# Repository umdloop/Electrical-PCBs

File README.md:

# ELECTRICAL PCBs

This repository contains all PCBs for UMD Loop's 2025-26 rover, Palamedes.

-----

## Guidelines
* Fork this repository for development, you can open a pull request to this repo to add your changes for everyone.
* Do NOT force push.
* Follow best practices (descriptive commit messages, well documented code, etc.)
* Add a new subdirectory for each PCB that is made

## Including Libraries
* The following libraries tab will include the Digikey, or product vendor component, CAD, Schematic, and/or Drawing for the components that are not found on KiCAD

## Including Datasheets
* The following datasheets tab includes useful information when referencing the components you need to include on the board

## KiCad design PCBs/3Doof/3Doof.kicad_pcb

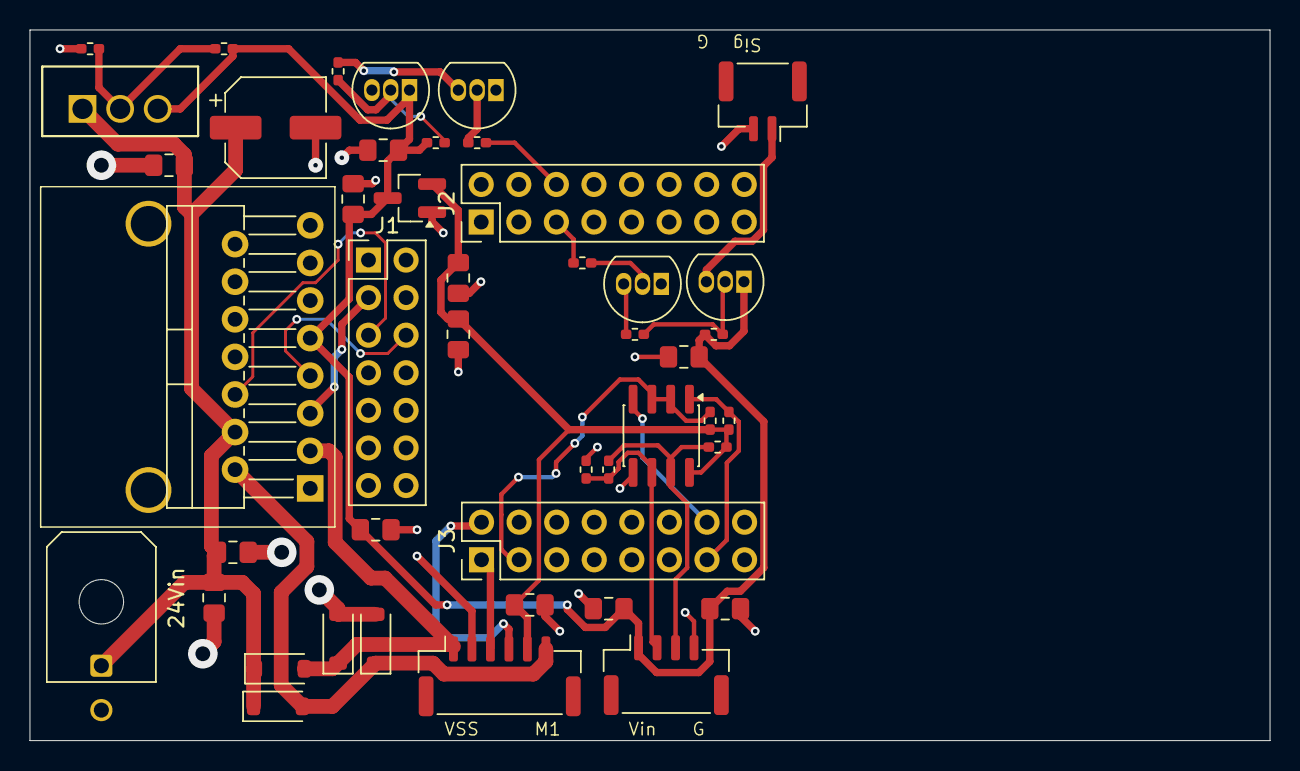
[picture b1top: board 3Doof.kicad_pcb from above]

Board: 2 copper layers, 83.8 x 48.0 mm, 47 parts (0 on the bottom side), 26 nets.

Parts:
24Vin: 24Vin; Molex_Micro-Fit_3.0_43045-0200_2x01_P3.00mm_Horizontal
CHBA1: 10uf; C_0805_2012Metric_Pad1.18x1.45mm_HandSolder
CHBA2: 100nf; C_0805_2012Metric_Pad1.18x1.45mm_HandSolder
CHBA3: 470uf; CP_Elec_6.3x7.7
CHBA4: 10u; C_0805_2012Metric_Pad1.18x1.45mm_HandSolder
CLD1: 10u; C_0805_2012Metric_Pad1.18x1.45mm_HandSolder
CRS1: 100n; C_0805_2012Metric_Pad1.18x1.45mm_HandSolder
CRS2, CRS3: 10u; C_0805_2012Metric_Pad1.18x1.45mm_HandSolder
CServoA1: 10u; C_0805_2012Metric_Pad1.18x1.45mm_HandSolder
CVin: 10u; C_0805_2012Metric_Pad1.18x1.45mm_HandSolder
CVregA1, CVregA3, CVregA4: 100n; C_0805_2012Metric_Pad1.18x1.45mm_HandSolder
DHBA1, DHBA2, DHBA3, DHBA4: 1N4148WT; D_SOD-123
H1, H2: MountingHole; MountingHole_3.2mm_M3
J1: Conn_02x07_Odd_Even; PinHeader_2x07_P2.54mm_Vertical
J2, J3: Conn_02x08_Odd_Even; PinHeader_2x08_P2.54mm_Vertical
J9: Laser Diode; JST_GH_SM02B-GHS-TB_1x02-1MP_P1.25mm_Horizontal
J12: RS485; JST_GH_SM04B-GHS-TB_1x04-1MP_P1.25mm_Horizontal
J14: HBA; JST_GH_SM06B-GHS-TB_1x06-1MP_P1.25mm_Horizontal
LaserDiodeT1: S8550; TO-92_Inline
Q1: QServoA; TO-92_Inline
Q6: LaserDiodeT; TO-92_Inline
QServoA1: S8550; TO-92_Inline
RLD1, RLD5: 220; R_0402_1005Metric_Pad0.72x0.64mm_HandSolder
RLD2: 330; R_0402_1005Metric_Pad0.72x0.64mm_HandSolder
RLD3: 680; R_0402_1005Metric_Pad0.72x0.64mm_HandSolder
RRS2, RRS3: 10K; R_0402_1005Metric_Pad0.72x0.64mm_HandSolder
RRS4, RRS5: 20K; R_0402_1005Metric_Pad0.72x0.64mm_HandSolder
RRS6: 120; R_0402_1005Metric_Pad0.72x0.64mm_HandSolder
RServoA1: 220; R_0402_1005Metric_Pad0.72x0.64mm_HandSolder
RServoA2: 330; R_0402_1005Metric_Pad0.72x0.64mm_HandSolder
RServoA3, RServoA6: 680; R_0402_1005Metric_Pad0.72x0.64mm_HandSolder
U1: MAX485E; SOIC-8_3.9x4.9mm_P1.27mm
U2: LM7805_TO220; T03B
U3: LM7805_TO220; SOT-23_Handsoldering
UHBA1: L298N; l298n_with_heatsink

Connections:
+3.3V: CHBA4.1, CRS2.2, CVregA3.1, J2.16, J14.5, RRS2.1, RRS3.1, RRS5.1, U1.8 (VCC), U3.2 (Vout)
+5V: CHBA1.1, CLD1.2, CRS1.2, CRS3.1, CServoA1.2, CVregA4.1, J12.1, LaserDiodeT1.1 (E), QServoA1.1 (E), RLD2.2, RLD5.1, RServoA2.2, U2.3 (VO), U3.3 (Vin), UHBA1.9 (Vss)
+24V: 24Vin.1, CHBA2.1, CHBA3.1, CVin.1, CVregA1.2, DHBA1.1 (K), DHBA3.1 (K), U2.1 (VI), UHBA1.4 (Vs)
/9: J1.3, UHBA1.5 (IN1)
/10: J1.6, UHBA1.7 (IN2)
/11: J1.5, UHBA1.6 (EnA)
/33: J3.13, RRS3.2, U1.1 (RO)
/35: J3.14, U1.4 (DI)
/41: J3.3, RRS2.2, U1.2 (~RE), U1.3 (DE)
/42: J3.2, J14.4
/43: J3.1, J14.3
/58: J2.5, RLD1.1
/59: J2.6, RServoA1.1
GND: 24Vin.2, CHBA1.2, CHBA2.2, CHBA3.2, CHBA4.2, CLD1.1, CRS1.1, CRS2.1, CRS3.2, CServoA1.1, CVin.2, CVregA1.1, CVregA3.2, CVregA4.2, DHBA2.2 (A), DHBA4.2 (A), J2.15, J9.2, J12.4, J14.2, Q1.1 (E), Q6.1 (E), RRS4.2, RServoA6.1, U1.5 (GND), U3.1 (GND), UHBA1.1 (SENSE_A), UHBA1.8 (GND), UHBA1.15 (SENSE_B)
unnamed: DHBA1.2 (A), DHBA2.1 (K), J14.6, UHBA1.2 (OUT1)
unnamed: DHBA3.2 (A), DHBA4.1 (K), J14.1, UHBA1.3 (OUT2)
unnamed: J9.1, LaserDiodeT1.3 (C)
unnamed: J12.2, RRS4.1, RRS6.1, U1.6 (A)
unnamed: J12.3, RRS5.2, RRS6.2, U1.7 (B)
unnamed: LaserDiodeT1.2 (B), RLD2.1, RLD3.2
unnamed: Q1.2 (B), RServoA1.2
unnamed: Q1.3 (C), RServoA3.1
unnamed: Q6.2 (B), RLD1.2
unnamed: Q6.3 (C), RLD3.1
unnamed: QServoA1.2 (B), RServoA2.1, RServoA3.2
unnamed: RLD5.2, RServoA6.2, U2.2 (GND)

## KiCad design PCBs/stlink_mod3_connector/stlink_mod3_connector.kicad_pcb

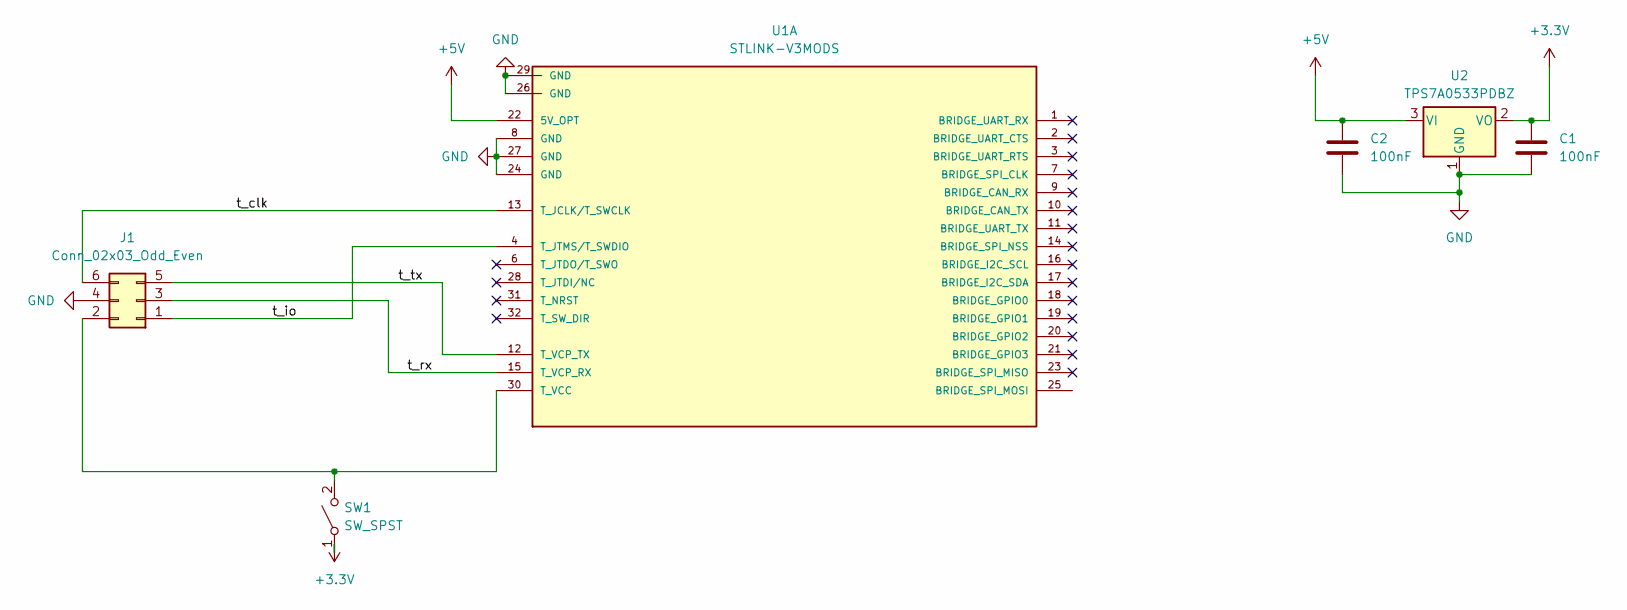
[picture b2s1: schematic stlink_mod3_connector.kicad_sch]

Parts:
C1, C2: 100nF; C_0805_2012Metric_Pad1.18x1.45mm_HandSolder
J1: Conn_02x03_Odd_Even; PinHeader_2x03_P2.54mm_Horizontal
SW1: SW_SPST; slide_switch_2_pin
U1: STLINK-V3MODS; MODULE_STLINK-V3MODS; PARTREV 1; DigiKey_Part_Number 497-STLINK-V3MODS-ND
U2: TPS7A0533PDBZ; SOT-23

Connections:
+3.3V: C1.1, SW1.1 (A), U2.2 (VO)
+5V: C2.1, U1.22 (5V_OPT), U2.3 (VI)
/t_clk: J1.6, U1.13 (T_JCLK/T_SWCLK)
/t_io: J1.1, U1.4 (T_JTMS/T_SWDIO)
/t_rx: J1.3, U1.15 (T_VCP_RX)
/t_tx: J1.5, U1.12 (T_VCP_TX)
GND: C1.2, C2.2, J1.4, U1.8 (GND), U1.24 (GND), U1.26 (GND), U1.27 (GND), U1.29 (GND), U2.1 (GND)
unnamed: J1.2, SW1.2 (B), U1.30 (T_VCC)

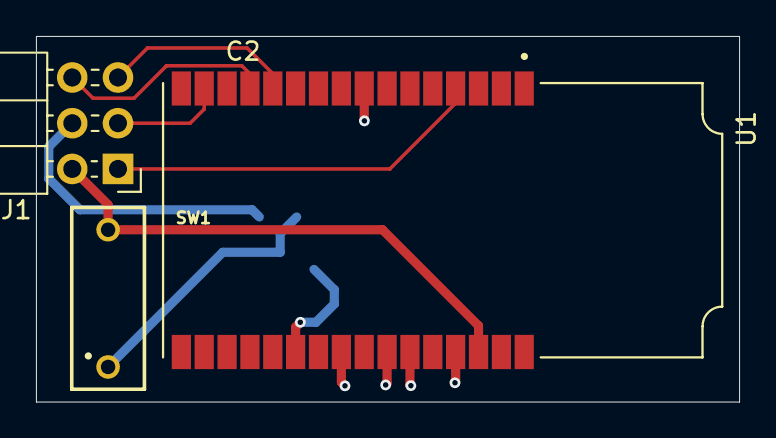
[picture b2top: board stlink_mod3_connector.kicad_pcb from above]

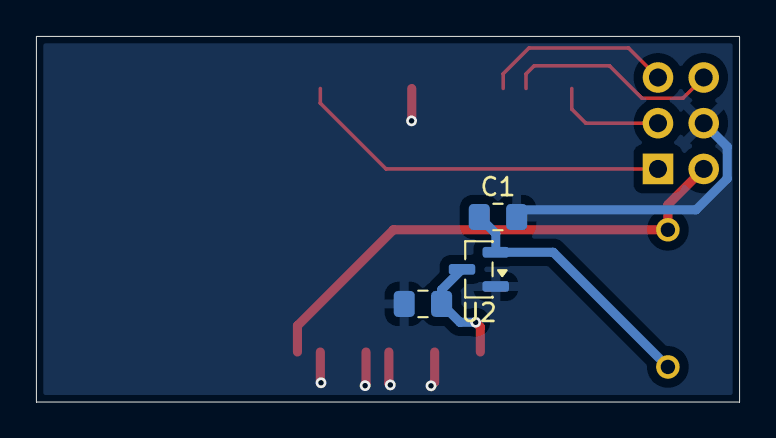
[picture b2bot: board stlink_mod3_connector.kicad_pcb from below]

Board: 2 copper layers, 39.1 x 20.3 mm, 6 parts (3 on the bottom side), 8 nets.

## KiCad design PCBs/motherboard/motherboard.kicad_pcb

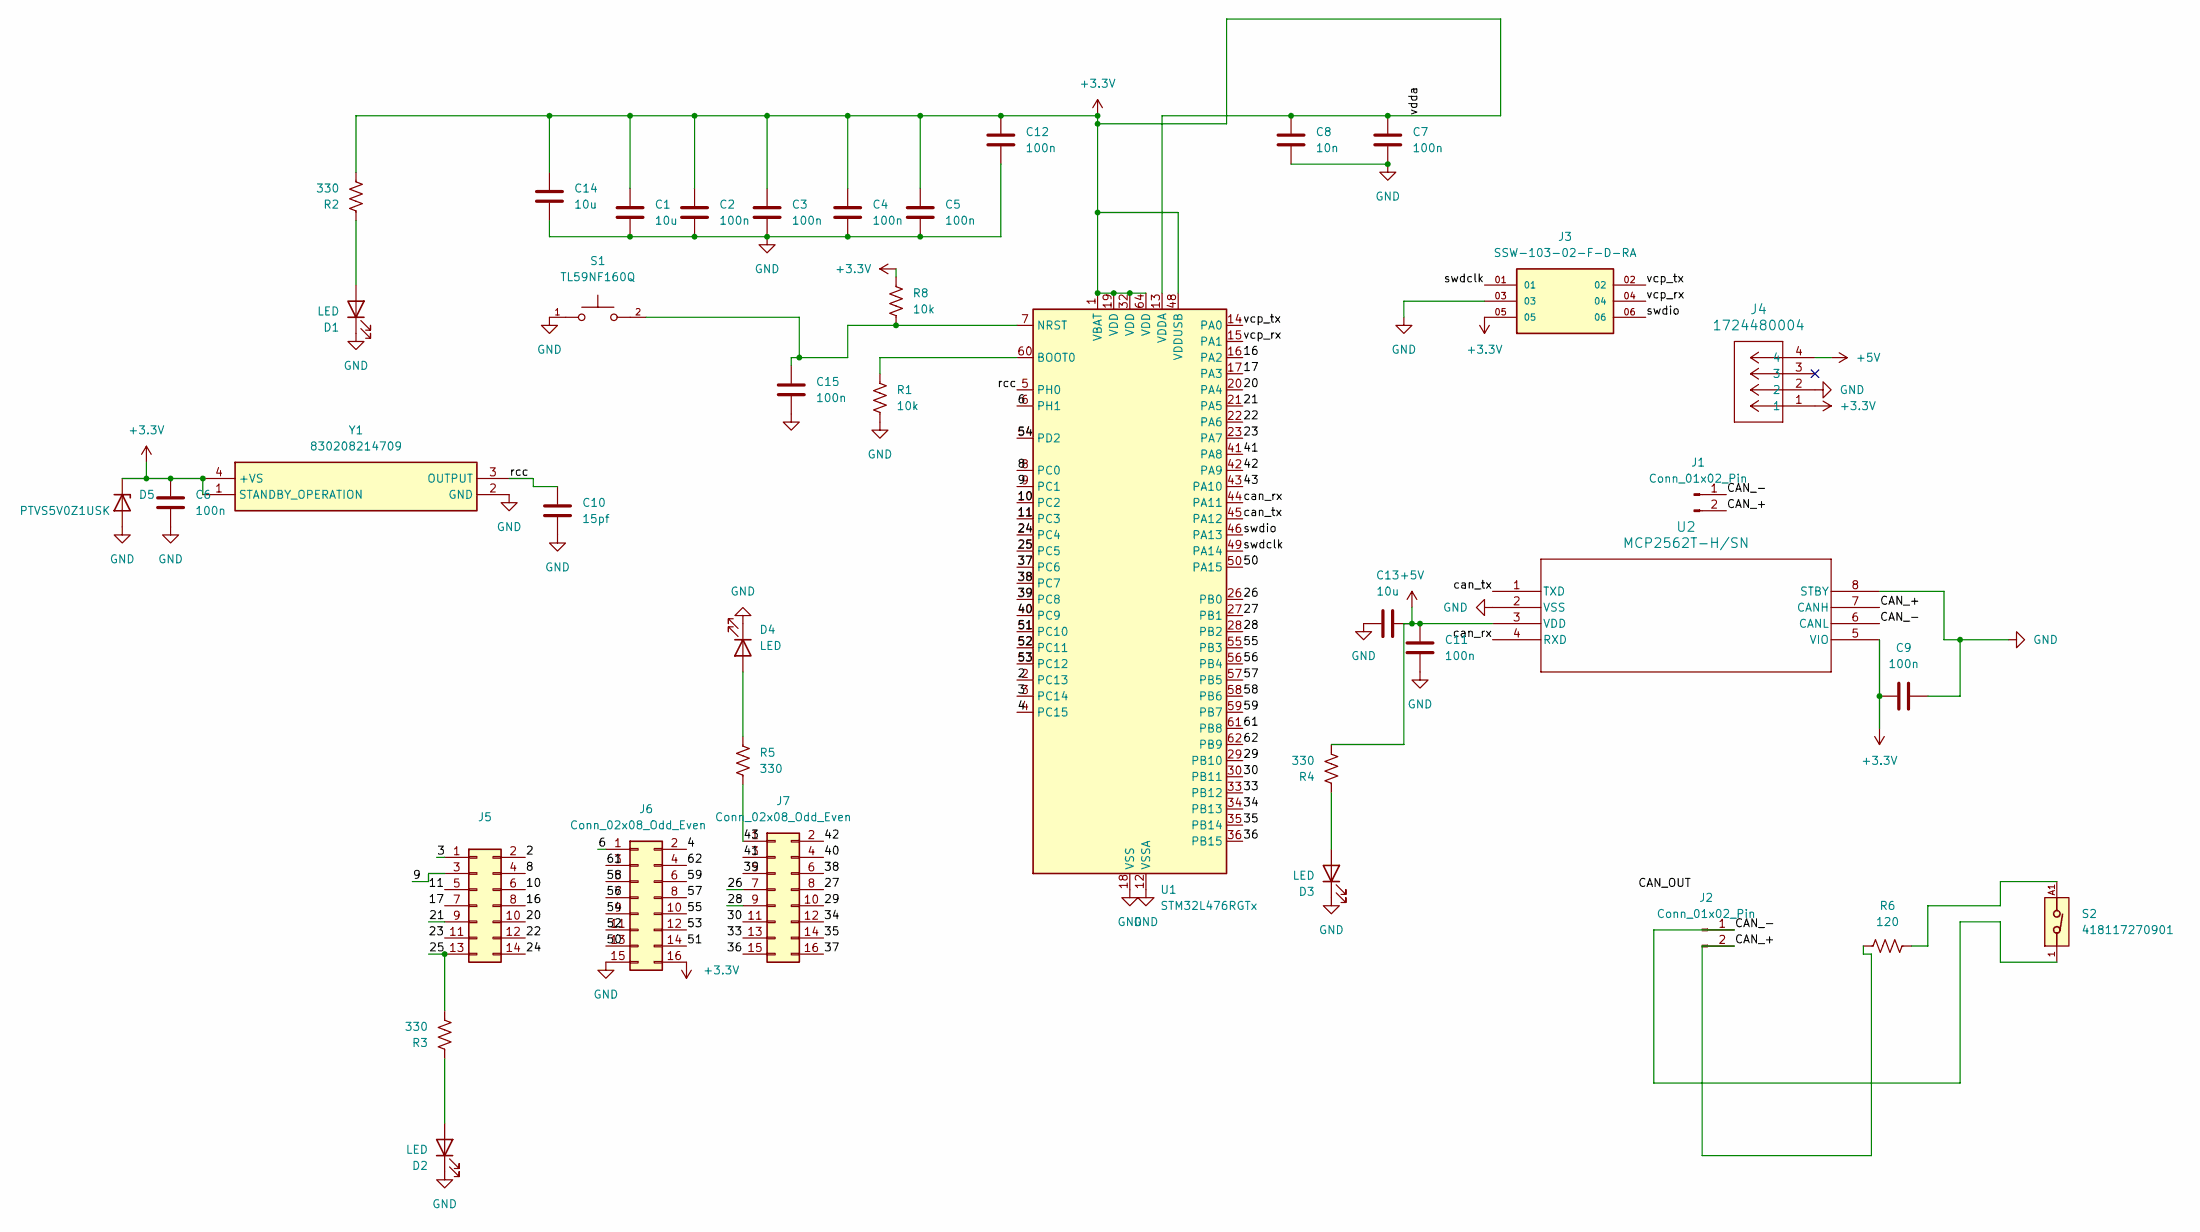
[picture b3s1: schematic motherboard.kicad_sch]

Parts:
C1, C13, C14: 10u; C_0805_2012Metric_Pad1.18x1.45mm_HandSolder
C2, C3, C4, C5, C6, C7, C9, C11, C12, C15: 100n; C_0805_2012Metric_Pad1.18x1.45mm_HandSolder
C8: 10n; C_0805_2012Metric_Pad1.18x1.45mm_HandSolder
C10: 15pf; C_0402_1005Metric_Pad0.74x0.62mm_HandSolder
D1, D2, D3, D4: LED; small_led
D5: PTVS5V0Z1USK; P37_SOD-123FL
J1, J2: Conn_01x02_Pin; can_molex_header
J3: SSW-103-02-F-D-RA; debug_header; PARTREV R
J4: 1724480004; power_header
J5: Conn_02x07_Odd_Even; PinHeader_2x07_P2.54mm_Vertical
J6, J7: Conn_02x08_Odd_Even; PinHeader_2x08_P2.54mm_Vertical
R1, R8: 10k; R_0402_1005Metric_Pad0.72x0.64mm_HandSolder
R2, R3, R4, R5: 330; R_0805_2012Metric_Pad1.20x1.40mm_HandSolder
R6: 120; R_0402_1005Metric_Pad0.72x0.64mm_HandSolder
S1: TL59NF160Q; reset_button; PARTREV G
S2: 418117270901; slide_switch_2_pin
U1: STM32L476RGTx; LQFP-64_10x10mm_P0.5mm
U2: MCP2562T-H/SN; can_transceiver
Y1: 830208214709; oscillator; Mouser Part Number 710-830208214709

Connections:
+3.3V: C1.1, C2.1, C3.1, C4.1, C5.1, C6.1, C7.1, C8.1, C9.1, C12.1, C14.1, D5.1 (K), J3.05, J4.1, J6.16, R2.2, R8.1, U1.1 (VBAT), U1.13 (VDDA), U1.19 (VDD), U1.32 (VDD), U1.48 (VDDUSB), U1.64 (VDD), U2.5 (VIO), Y1.1 (STANDBY_OPERATION), Y1.4 (+VS)
+5V: C11.2, C13.2, J4.4, R4.2, U2.3 (VDD)
/2: J5.2, U1.2 (PC13)
/3: J5.1, U1.3 (PC14)
/4: J6.2, U1.4 (PC15)
/6: J6.1, U1.6 (PH1)
/8: J5.4, U1.8 (PC0)
/9: J5.3, U1.9 (PC1)
/10: J5.6, U1.10 (PC2)
/11: J5.5, U1.11 (PC3)
/16: J5.8, U1.16 (PA2)
/17: J5.7, U1.17 (PA3)
/20: J5.10, U1.20 (PA4)
/21: J5.9, U1.21 (PA5)
/22: J5.12, U1.22 (PA6)
/23: J5.11, U1.23 (PA7)
/24: J5.14, U1.24 (PC4)
/25: J5.13, R3.2, U1.25 (PC5)
/26: J7.7, U1.26 (PB0)
/27: J7.8, U1.27 (PB1)
/28: J7.9, U1.28 (PB2)
/29: J7.10, U1.29 (PB10)
/30: J7.11, U1.30 (PB11)
/33: J7.13, U1.33 (PB12)
/34: J7.12, U1.34 (PB13)
/35: J7.14, U1.35 (PB14)
/36: J7.15, U1.36 (PB15)
/37: J7.16, U1.37 (PC6)
/38: J7.6, U1.38 (PC7)
/39: J7.5, U1.39 (PC8)
/40: J7.4, U1.40 (PC9)
/41: J7.3, U1.41 (PA8)
/42: J7.2, U1.42 (PA9)
/43: J7.1, R5.2, U1.43 (PA10)
/50: J6.13, U1.50 (PA15)
/51: J6.14, U1.51 (PC10)
/52: J6.11, U1.52 (PC11)
/53: J6.12, U1.53 (PC12)
/54: J6.9, U1.54 (PD2)
/55: J6.10, U1.55 (PB3)
/56: J6.7, U1.56 (PB4)
/57: J6.8, U1.57 (PB5)
/58: J6.5, U1.58 (PB6)
/59: J6.6, U1.59 (PB7)
/61: J6.3, U1.61 (PB8)
/62: J6.4, U1.62 (PB9)
/CAN_+: J1.2, J2.2, R6.1, U2.7 (CANH)
/CAN_-: J1.1, J2.1, S2.1, U2.6 (CANL)
/can_rx: U1.44 (PA11), U2.4 (RXD)
/can_tx: U1.45 (PA12), U2.1 (TXD)
/rcc: C10.1, U1.5 (PH0), Y1.3 (OUTPUT)
/swdclk: J3.01, U1.49 (PA14)
/swdio: J3.06, U1.46 (PA13)
/vcp_rx: J3.04, U1.15 (PA1)
/vcp_tx: J3.02, U1.14 (PA0)
GND: C1.2, C2.2, C3.2, C4.2, C5.2, C6.2, C7.2, C8.2, C9.2, C10.2, C11.1, C12.2, C13.1, C14.2, C15.2, D1.1 (K), D2.1 (K), D3.1 (K), D4.1 (K), D5.2 (A), J3.03, J4.2, J6.15, R1.2, S1.1, U1.12 (VSSA), U1.18 (VSS), U1.31 (VSS), U1.47 (VSS), U1.63 (VSS), U2.2 (VSS), U2.8 (STBY), Y1.2 (GND)
unnamed: D1.2 (A), R2.1
unnamed: D2.2 (A), R3.1
unnamed: D3.2 (A), R4.1
unnamed: D4.2 (A), R5.1
unnamed: R6.2, S2.A1
unnamed: R1.1, U1.60 (BOOT0)
unnamed: C15.1, R8.2, S1.2, U1.7 (NRST)

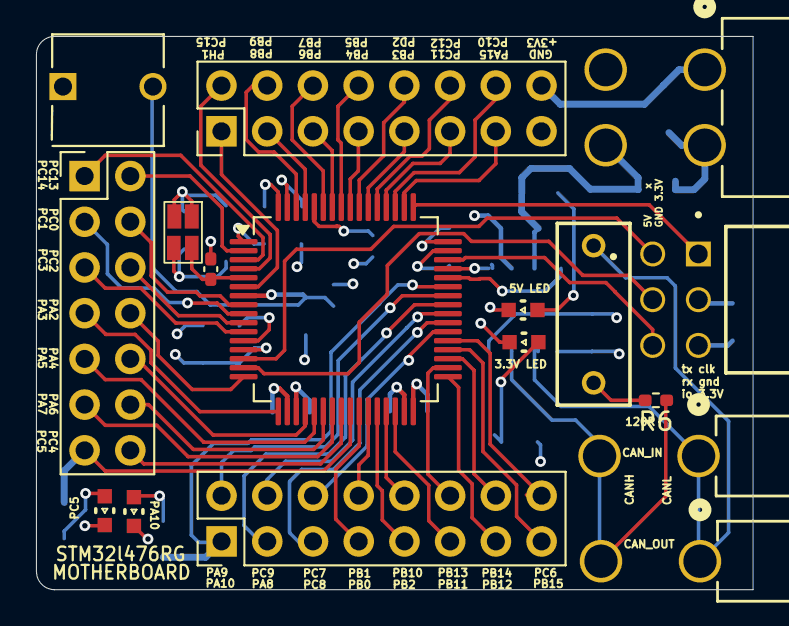
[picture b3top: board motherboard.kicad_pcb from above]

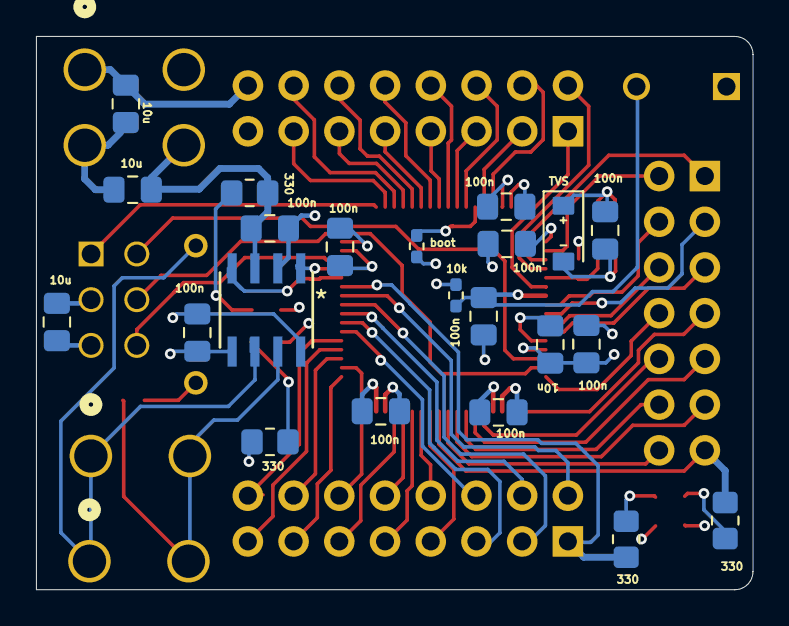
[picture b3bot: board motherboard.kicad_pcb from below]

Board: 4 copper layers, 39.8 x 30.7 mm, 39 parts (22 on the bottom side), 63 nets.

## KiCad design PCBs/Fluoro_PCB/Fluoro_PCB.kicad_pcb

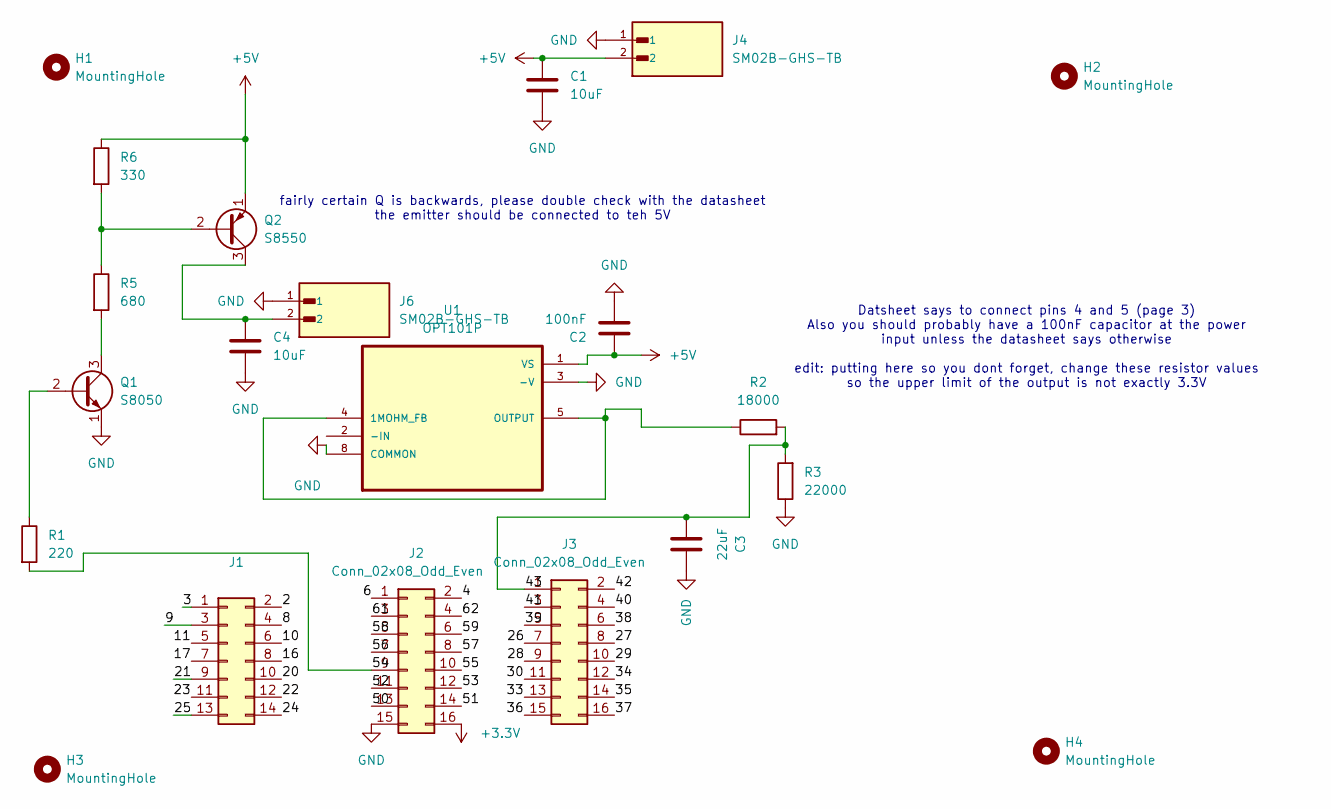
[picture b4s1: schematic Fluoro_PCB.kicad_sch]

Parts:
C1, C4: 10uF; C_0805_2012Metric
C2: 100nF; C_0805_2012Metric
C3: 22uF; C_0805_2012Metric
H1, H2, H3, H4: MountingHole; MountingHole_3.2mm_M3_DIN965
J1: Conn_02x07_Odd_Even; PinHeader_2x07_P2.54mm_Vertical
J2, J3: Conn_02x08_Odd_Even; PinHeader_2x08_P2.54mm_Vertical
J4, J6: SM02B-GHS-TB; JST_GH_SM02B-GHS-TB_1x02-1MP_P1.25mm_Horizontal
Q1: S8050; TO-92_Inline
Q2: S8550; TO-92_Inline
R1: 220; R_0805_2012Metric
R2: 18000; R_Axial_DIN0207_L6.3mm_D2.5mm_P7.62mm_Horizontal
R3: 22000; R_Axial_DIN0207_L6.3mm_D2.5mm_P7.62mm_Horizontal
R5: 680; R_0805_2012Metric
R6: 330; R_0805_2012Metric
U1: OPT101P; DIP762W46P254L952H419Q8

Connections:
+3.3V: J2.16
+5V: C1.1, C2.1, J4.2, Q2.1 (E), R6.1, U1.1 (VS)
/2: J1.2
/3: J1.1
/4: J2.2
/8: J1.4
/9: J1.3
/10: J1.6
/11: J1.5
/16: J1.8
/17: J1.7
/20: J1.10
/21: J1.9
/22: J1.12
/23: J1.11
/24: J1.14
/25: J1.13
/27: J3.8
/29: J3.10
/30: J3.11
/33: J3.13
/34: J3.12
/35: J3.14
/36: J3.15
/37: J3.16
/38: J3.6
/39: J3.5
/40: J3.4
/41: J3.3
/42: J3.2
/43: C3.1, J3.1, R2.2, R3.2
/50: J2.13
/51: J2.14
/52: J2.11
/53: J2.12
/54: J2.9, R1.2
/55: J2.10
/56: J2.7
/57: J2.8
/58: J2.5
/59: J2.6
/61: J2.3
/62: J2.4
GND: C1.2, C2.2, C3.2, C4.2, J2.15, J4.1, J6.1, Q1.1 (E), R3.1, U1.3 (-V), U1.8 (COMMON)
unnamed: Q1.2 (B), R1.1
unnamed: Q1.3 (C), R5.2
unnamed: Q2.2 (B), R5.1, R6.2
unnamed: C4.1, J6.2, Q2.3 (C)
unnamed: R2.1, U1.4 (1MOHM_FB), U1.5 (OUTPUT)

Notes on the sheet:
Datsheet says to connect pins 4 and 5 (page 3) Also you should probably have a 100nF capacitor at the power input unless the datasheet says otherwise edit: putting here so you dont forget, change these resistor values so the upper limit of the output is not exactly 3.3V
fairly certain Q is backwards, please double check with the datasheet the emitter should be connected to teh 5V

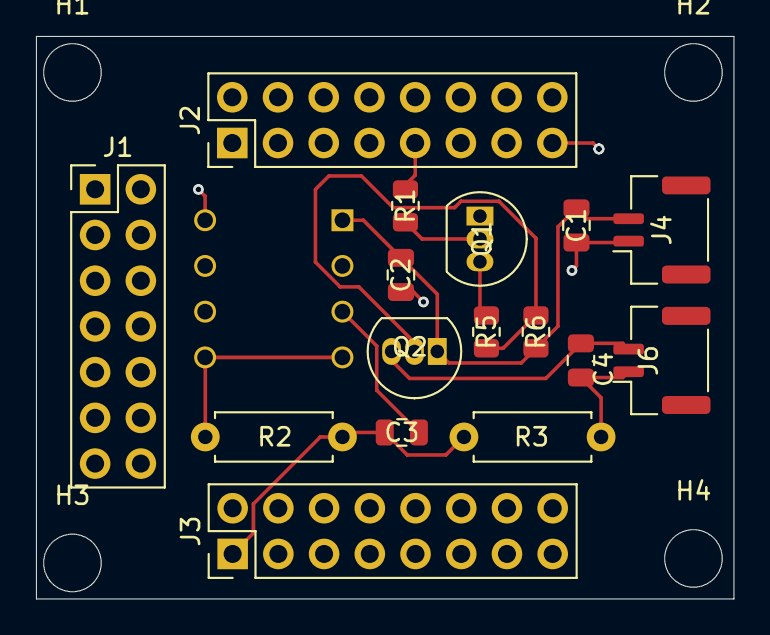
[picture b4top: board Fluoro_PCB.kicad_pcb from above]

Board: 2 copper layers, 38.8 x 31.2 mm, 21 parts (1 on the bottom side), 9 nets.

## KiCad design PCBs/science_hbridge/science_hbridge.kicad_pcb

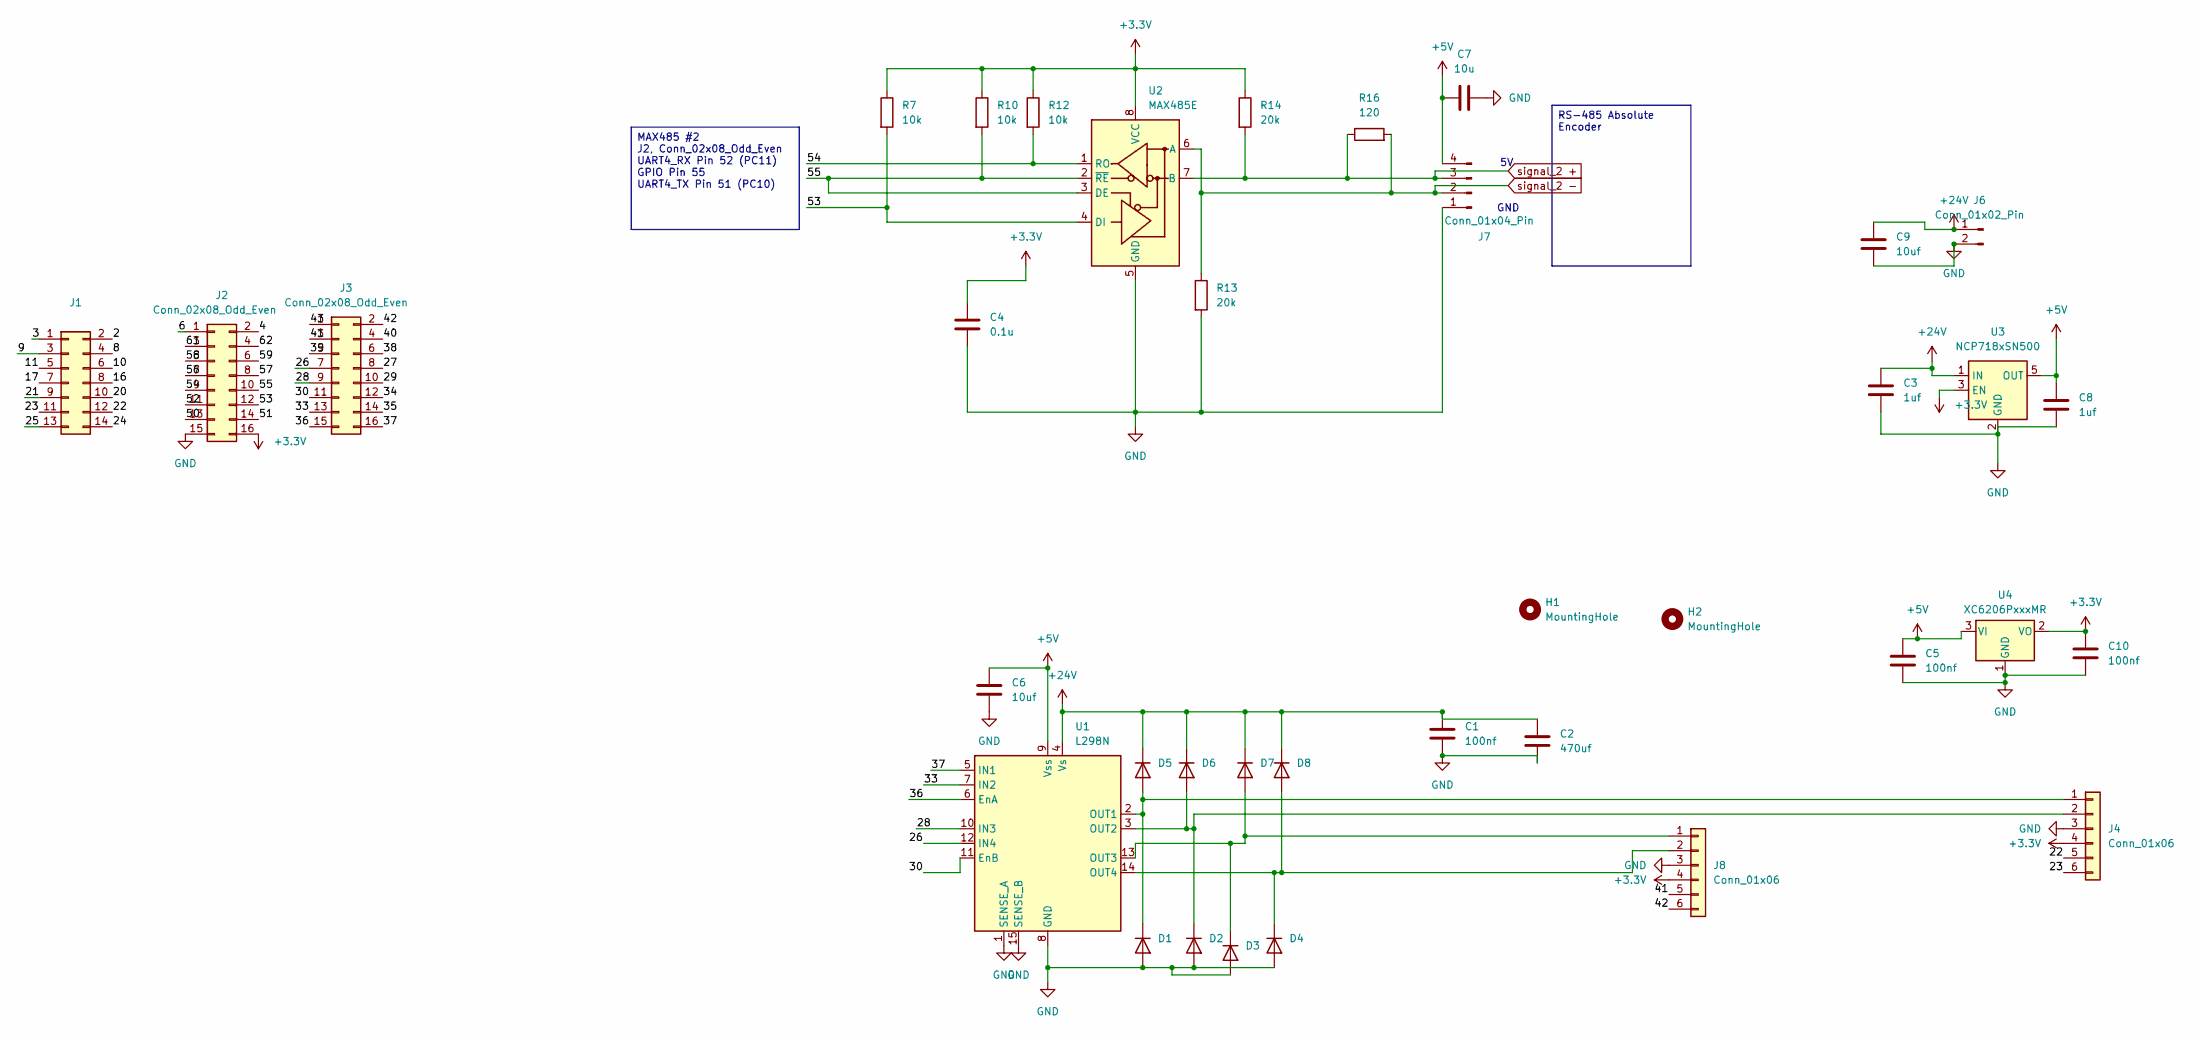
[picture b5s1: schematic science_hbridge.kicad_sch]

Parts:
C1, C5, C10: 100nf; C_0805_2012Metric_Pad1.18x1.45mm_HandSolder
C2: 470uf; CP_Elec_8x6.2
C3, C8: 1uf; C_0805_2012Metric_Pad1.18x1.45mm_HandSolder
C4: 0.1u; C_0402_1005Metric_Pad0.74x0.62mm_HandSolder
C6, C9: 10uf; C_0805_2012Metric_Pad1.18x1.45mm_HandSolder
C7: 10u; C_0805_2012Metric_Pad1.18x1.45mm_HandSolder
D1, D2, D3, D4, D5, D6, D7, D8: 1N4148WT; D_SOD-123
H1, H2: MountingHole; MountingHole_3.2mm_M3
J1: Conn_02x07_Odd_Even; PinHeader_2x07_P2.54mm_Vertical
J2, J3: Conn_02x08_Odd_Even; PinHeader_2x08_P2.54mm_Vertical
J4, J8: Conn_01x06; JST_GH_SM06B-GHS-TB_1x06-1MP_P1.25mm_Horizontal
J6: Conn_01x02_Pin; CONN_SD-43045-001_02_MOL
J7: Conn_01x04_Pin; JST_GH_SM04B-GHS-TB_1x04-1MP_P1.25mm_Horizontal
R7, R10, R12: 10k; R_0402_1005Metric_Pad0.72x0.64mm_HandSolder
R13, R14: 20k; R_0402_1005Metric_Pad0.72x0.64mm_HandSolder
R16: 120; R_0402_1005Metric_Pad0.72x0.64mm_HandSolder
U1: L298N; l298n_with_heatsink
U2: MAX485E; SOIC-8_3.9x4.9mm_P1.27mm
U3: NCP718xSN500; SOT-23-5
U4: XC6206PxxxMR; SOT-23-3

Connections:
+3.3V: C4.1, C10.1, J2.16, J4.4, J8.4, R7.1, R10.1, R12.1, R14.1, U2.8 (VCC), U3.3 (EN), U4.2 (VO)
+5V: C5.1, C6.1, C7.1, C8.1, J7.4, U1.9 (Vss), U3.5 (OUT), U4.3 (VI)
+24V: C1.1, C2.1, C3.1, C9.1, D5.1 (K), D6.1 (K), D7.1 (K), D8.1 (K), J6.1, U1.4 (Vs), U3.1 (IN)
/2: J1.2
/3: J1.1
/4: J2.2
/6: J2.1
/8: J1.4
/9: J1.3
/10: J1.6
/11: J1.5
/16: J1.8
/17: J1.7
/20: J1.10
/21: J1.9
/22: J1.12, J4.5
/23: J1.11, J4.6
/24: J1.14
/25: J1.13
/26: J3.7, U1.12 (IN4)
/27: J3.8
/28: J3.9, U1.10 (IN3)
/29: J3.10
/30: J3.11, U1.11 (EnB)
/33: J3.13, U1.7 (IN2)
/34: J3.12
/35: J3.14
/36: J3.15, U1.6 (EnA)
/37: J3.16, U1.5 (IN1)
/38: J3.6
/39: J3.5
/40: J3.4
/41: J3.3, J8.5
/42: J3.2, J8.6
/43: J3.1
/50: J2.13
/51: J2.14
/52: J2.11
/53: J2.12, R7.2, U2.4 (DI)
/54: J2.9, R12.2, U2.1 (RO)
/55: J2.10, R10.2, U2.2 (~RE), U2.3 (DE)
/56: J2.7
/57: J2.8
/58: J2.5
/59: J2.6
/61: J2.3
/62: J2.4
GND: C1.2, C2.2, C3.2, C4.2, C5.2, C6.2, C7.2, C8.2, C9.2, C10.2, D1.2 (A), D2.2 (A), D3.2 (A), D4.2 (A), J2.15, J4.3, J6.2, J7.1, J8.3, R13.2, U1.1 (SENSE_A), U1.8 (GND), U1.15 (SENSE_B), U2.5 (GND), U3.2 (GND), U4.1 (GND)
unnamed: D1.1 (K), D5.2 (A), J4.1, U1.2 (OUT1)
unnamed: D2.1 (K), D6.2 (A), J4.2, U1.3 (OUT2)
unnamed: D3.1 (K), D7.2 (A), J8.1, U1.13 (OUT3)
unnamed: D4.1 (K), D8.2 (A), J8.2, U1.14 (OUT4)
signal_2 +: J7.3, R14.2, R16.1, U2.7 (B)
signal_2 -: J7.2, R13.1, R16.2, U2.6 (A)

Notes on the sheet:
GND
MAX485 #2 J2, Conn_02x08_Odd_Even UART4_RX Pin 52 (PC11) GPIO Pin 55 UART4_TX Pin 51 (PC10)
RS-485 Absolute Encoder

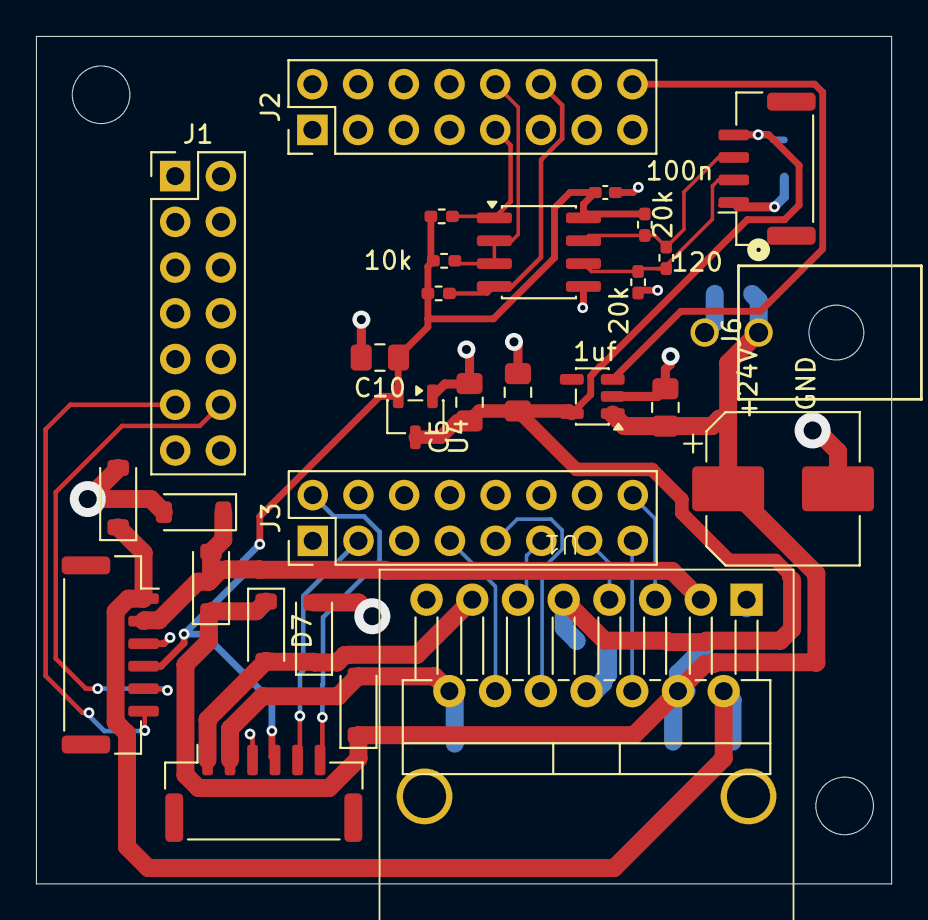
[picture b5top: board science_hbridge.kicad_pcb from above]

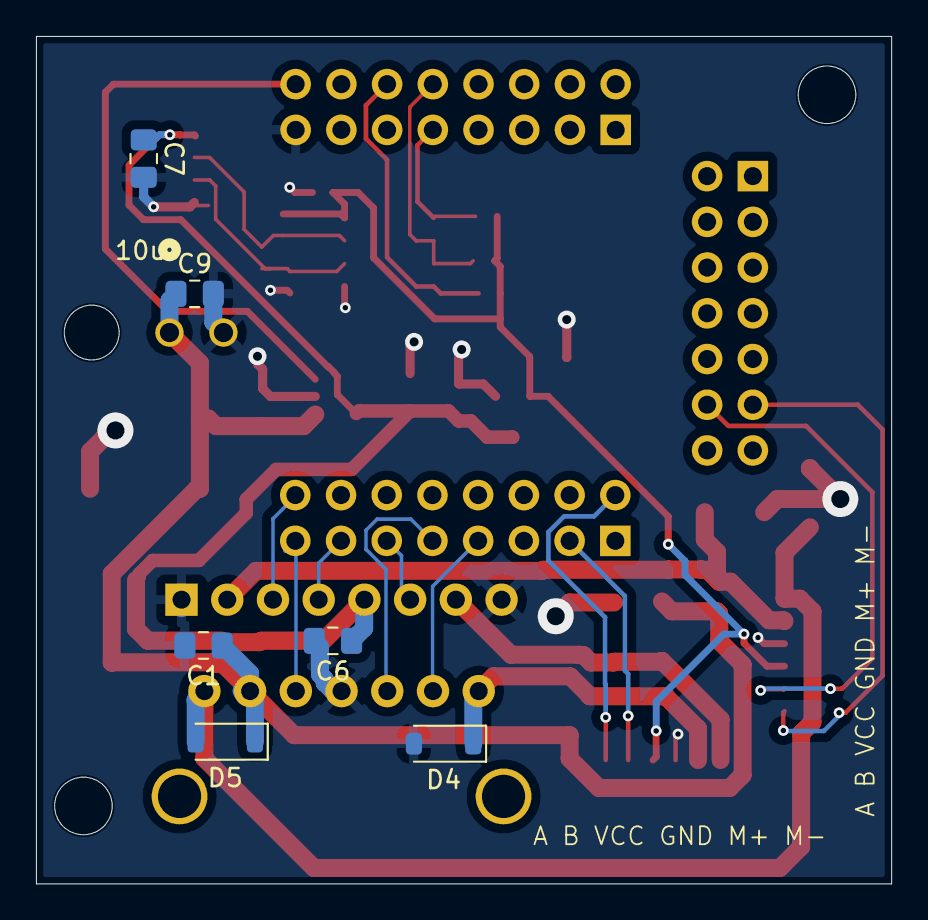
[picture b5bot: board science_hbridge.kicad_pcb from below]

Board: 2 copper layers, 47.5 x 47.1 mm, 37 parts (6 on the bottom side), 23 nets.

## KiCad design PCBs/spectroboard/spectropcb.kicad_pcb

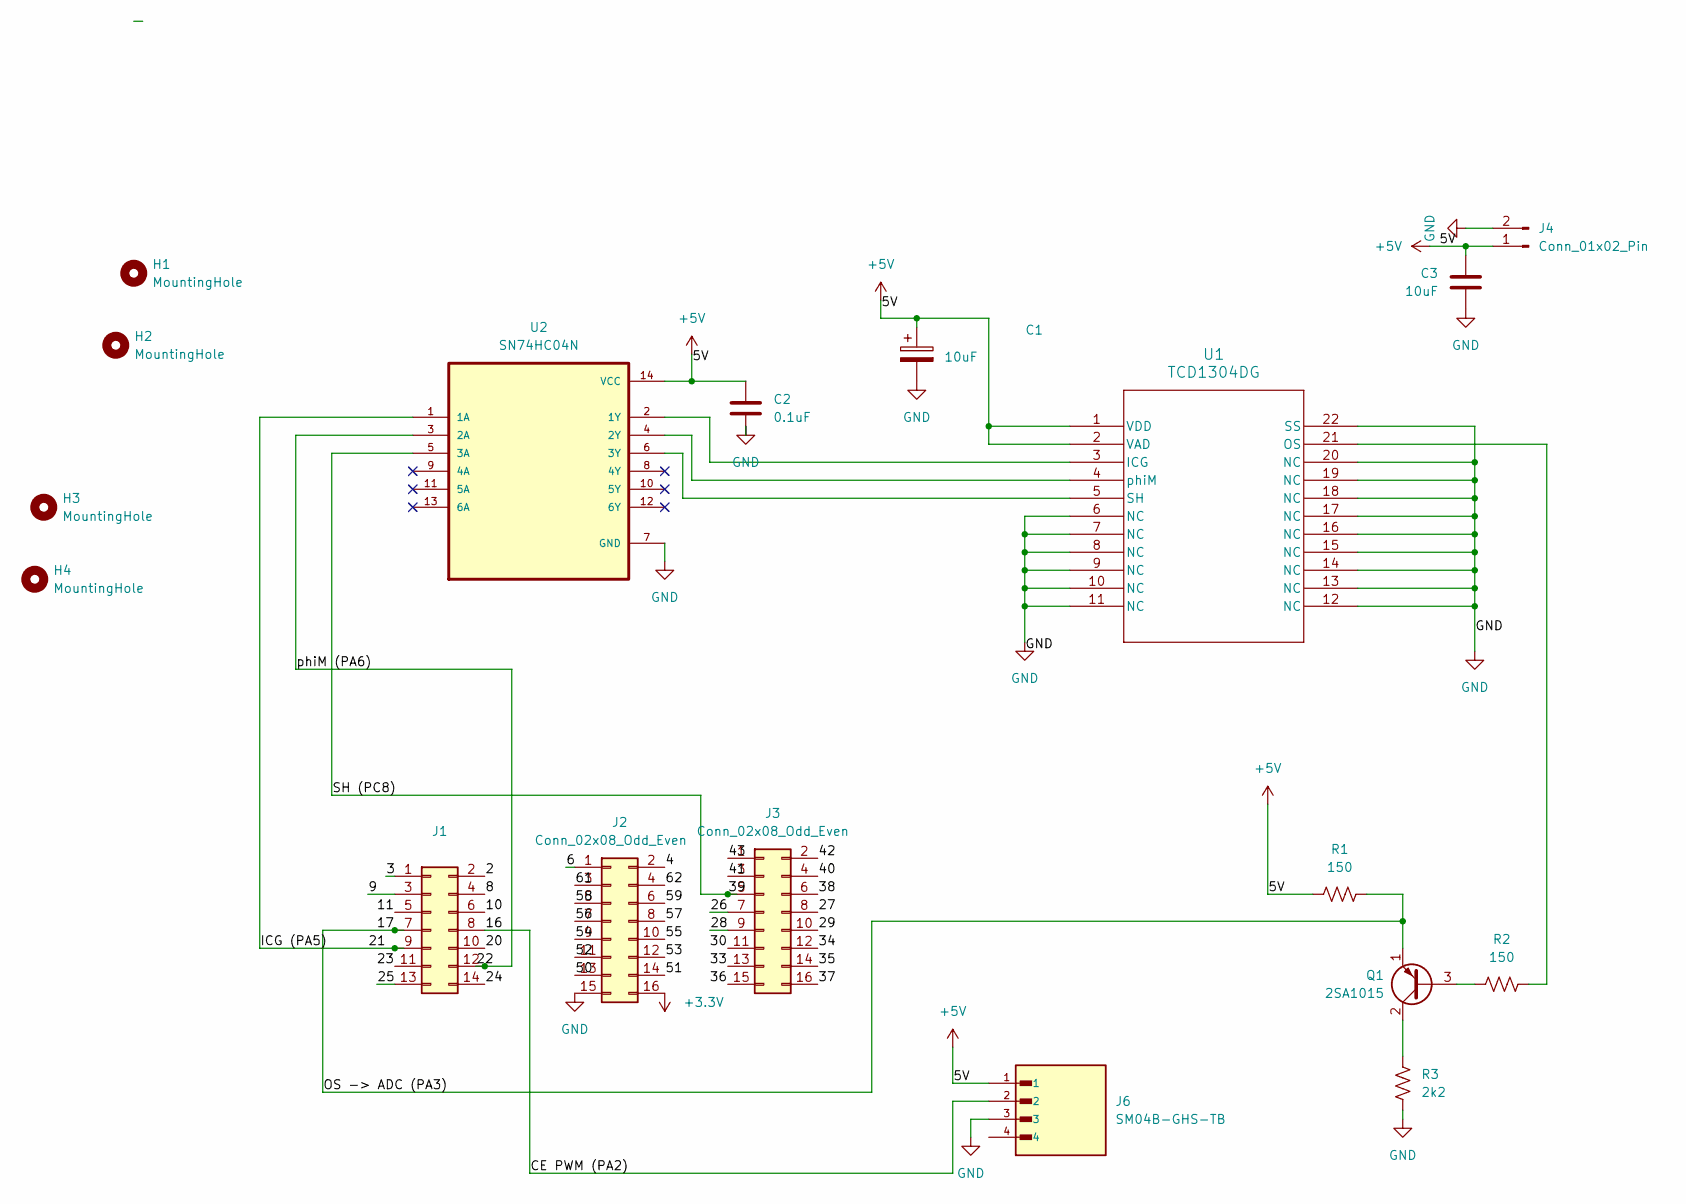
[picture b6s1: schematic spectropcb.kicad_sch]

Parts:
C1: 10uF; C_0805_2012Metric
C2: 0.1uF; C_1206_3216Metric
C3: 10uF; C_1206_3216Metric
H1, H2, H3, H4: MountingHole; MountingHole_3.2mm_M3
J1: Conn_02x07_Odd_Even; PinHeader_2x07_P2.54mm_Vertical
J2, J3: Conn_02x08_Odd_Even; PinHeader_2x08_P2.54mm_Vertical
J4: Conn_01x02_Pin; JST_GH_SM02B-GHS-TB_1x02-1MP_P1.25mm_Horizontal
J6: SM04B-GHS-TB; JST_SM04B-GHS-TB
Q1: 2SA1015; TO-92_Inline
R1, R2: 150; R_0805_2012Metric
R3: 2k2; R_0805_2012Metric
U1: TCD1304DG; WDIP22-G-400-2.54H_TOS
U2: SN74HC04N; DIP794W45P254L1969H508Q14

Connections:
+3.3V: J2.16
+5V: C1.1, C2.1, C3.1, J4.1, J6.1, R1.1, U1.1 (VDD), U1.2 (VAD), U2.14 (VCC)
/2: J1.2
/3: J1.1
/4: J2.2
/6: J2.1
/8: J1.4
/9: J1.3
/10: J1.6
/11: J1.5
/16: J1.8, J6.2
/17: J1.7, Q1.1 (E), R1.2
/20: J1.10
/21: J1.9, U2.1 (1A)
/22: J1.12, U2.3 (2A)
/23: J1.11
/24: J1.14
/25: J1.13
/26: J3.7
/27: J3.8
/28: J3.9
/29: J3.10
/30: J3.11
/33: J3.13
/34: J3.12
/35: J3.14
/36: J3.15
/37: J3.16
/38: J3.6
/39: J3.5, U2.5 (3A)
/40: J3.4
/41: J3.3
/42: J3.2
/43: J3.1
/50: J2.13
/51: J2.14
/52: J2.11
/53: J2.12
/54: J2.9
/55: J2.10
/56: J2.7
/57: J2.8
/58: J2.5
/59: J2.6
/61: J2.3
/62: J2.4
GND: C1.2, C2.2, C3.2, J2.15, J4.2, J6.3, R3.2, U1.6 (NC), U1.7 (NC), U1.8 (NC), U1.9 (NC), U1.10 (NC), U1.11 (NC), U1.12 (NC), U1.13 (NC), U1.14 (NC), U1.15 (NC), U1.16 (NC), U1.17 (NC), U1.18 (NC), U1.19 (NC), U1.20 (NC), U1.22 (SS), U2.7 (GND)
unnamed: Q1.3 (B), R2.1
unnamed: Q1.2 (C), R3.1
unnamed: U1.3 (ICG), U2.2 (1Y)
unnamed: R2.2, U1.21 (OS)
unnamed: U1.5 (SH), U2.6 (3Y)
unnamed: U1.4 (phiM), U2.4 (2Y)
